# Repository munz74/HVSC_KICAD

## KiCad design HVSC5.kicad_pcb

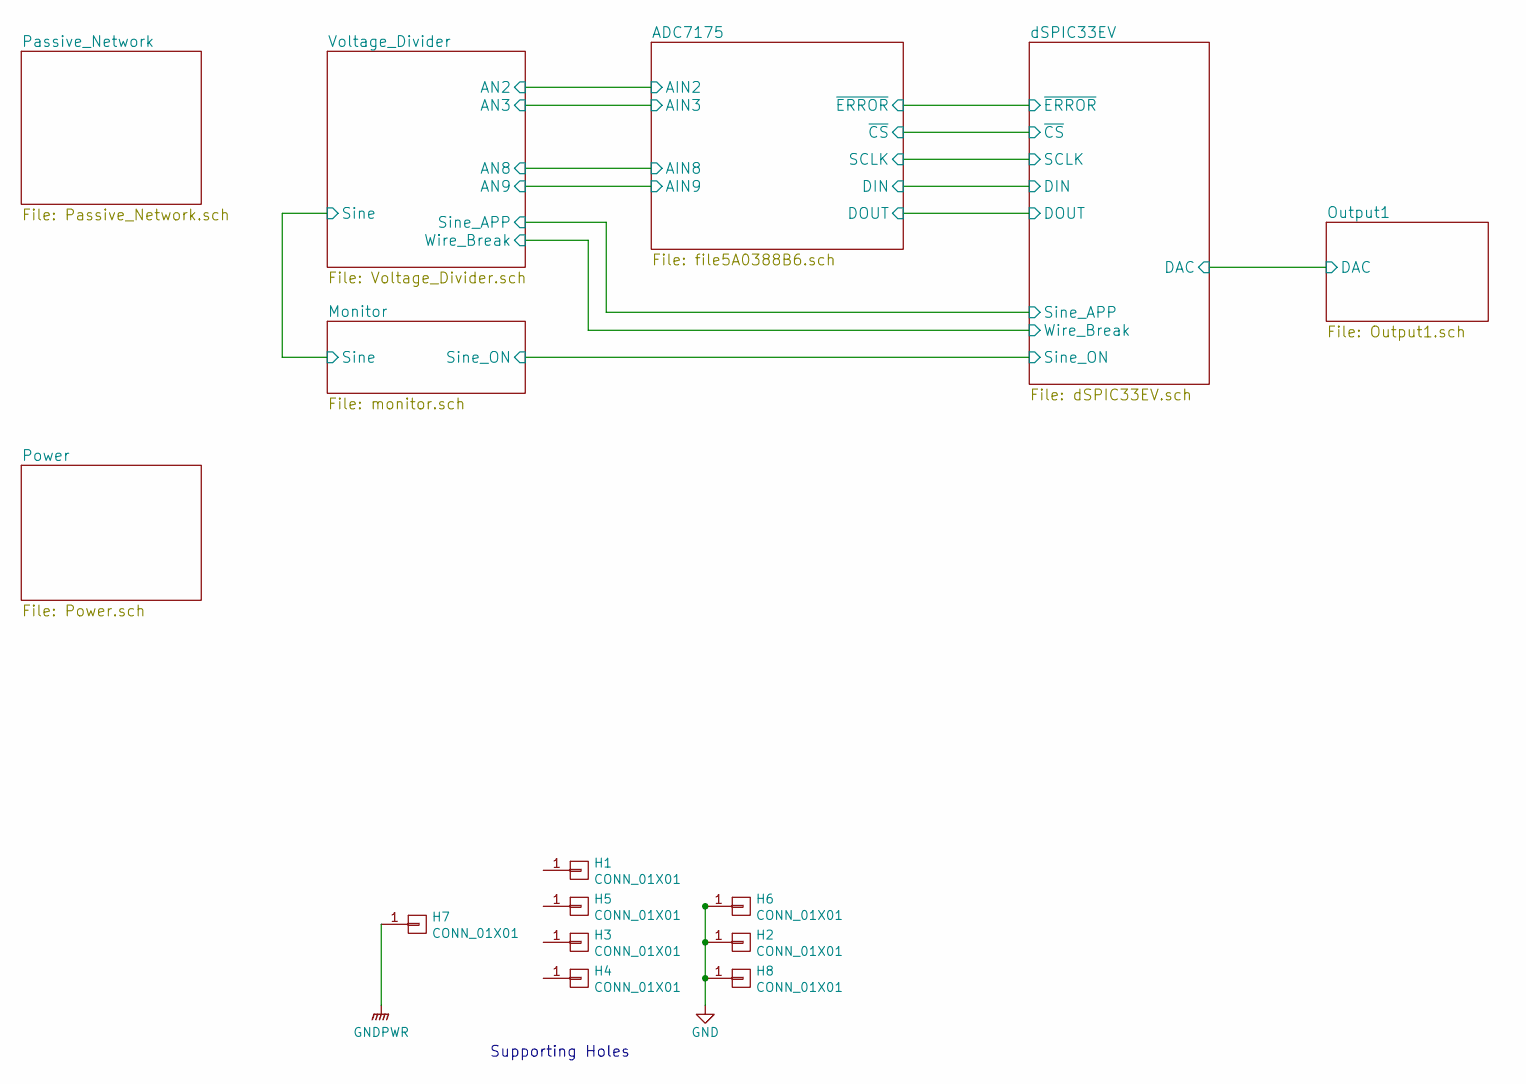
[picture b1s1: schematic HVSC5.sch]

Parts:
H1, H2, H3, H4, H5, H6, H7, H8: CONN_01X01; MountingHole_3.2mm_M3_Pad_Via

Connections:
GND: H2.1, H6.1, H8.1; also elsewhere on the board
GNDPWR: H7.1; also elsewhere on the board

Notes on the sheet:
Supporting Holes

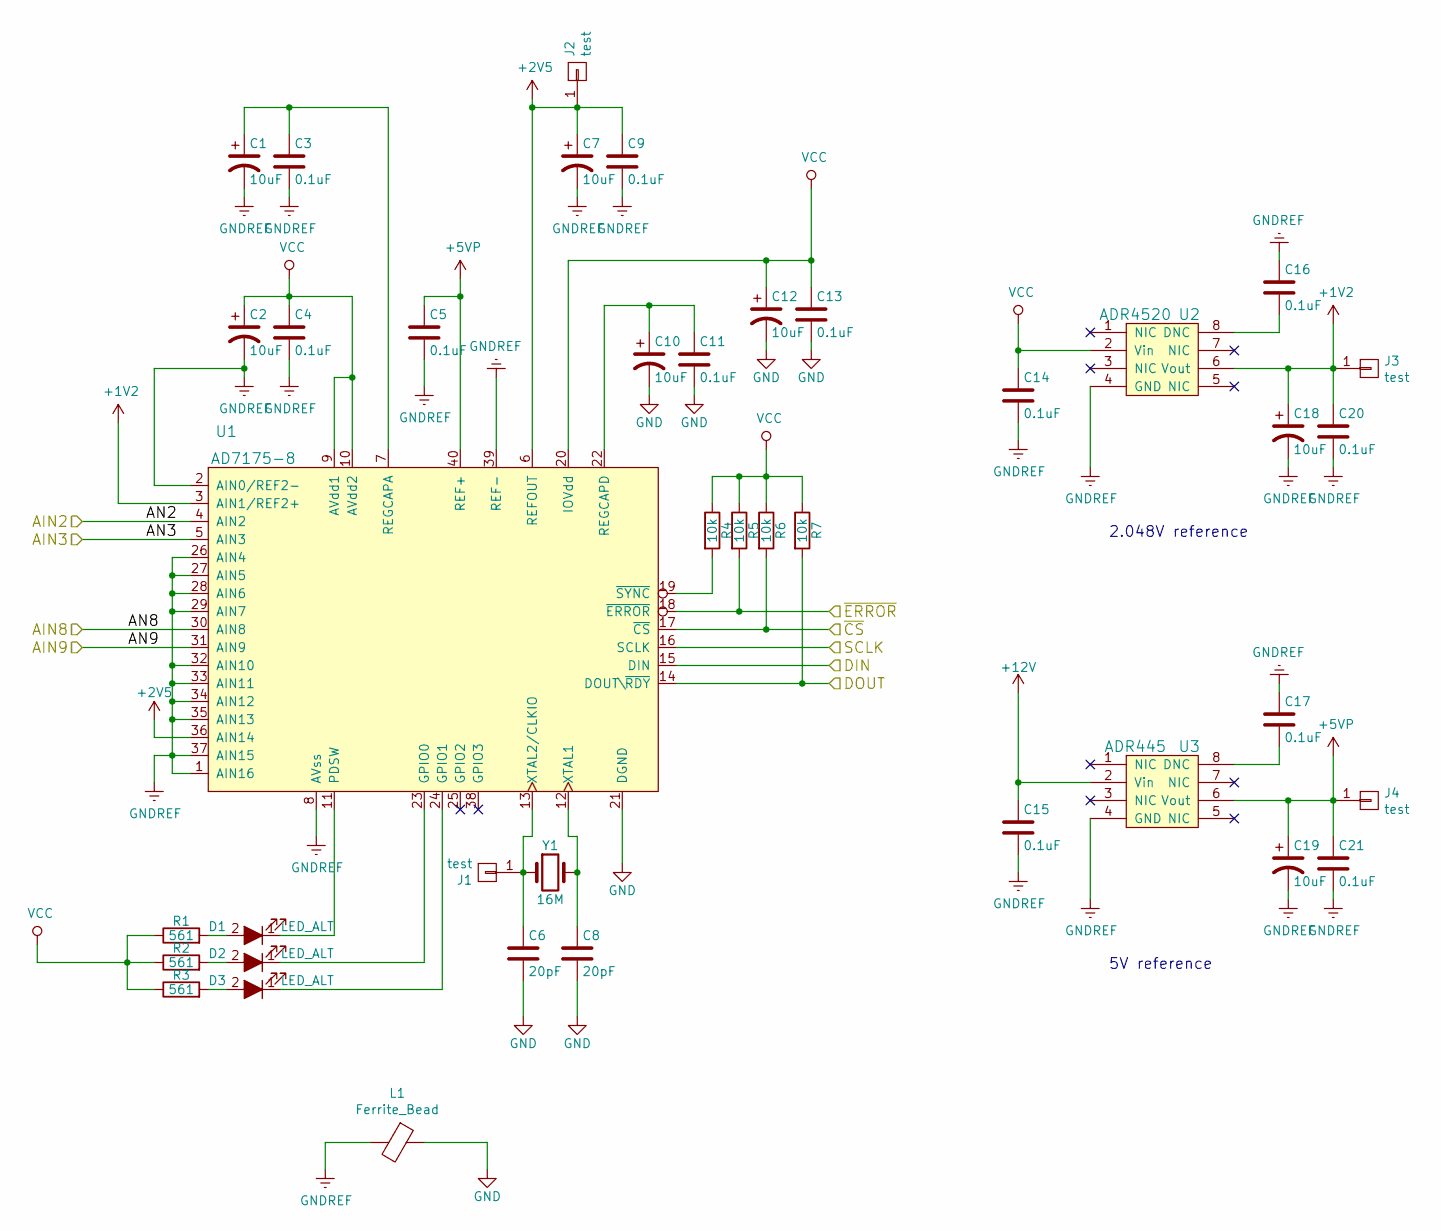
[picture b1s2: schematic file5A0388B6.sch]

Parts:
C1, C2, C7, C10, C12, C18, C19: 10uF; C_1812_HandSoldering_Polar
C3, C4, C5, C9, C11, C13, C14, C15, C16, C17, C20, C21: 0.1uF; C_0805_HandSoldering
C6, C8: 20pF; C_0805_HandSoldering
D1, D2, D3: LED_ALT; LED_0603_HandSoldering
J1, J2, J3, J4: test; Pin_Header_Straight_1x01_Pitch2.00mm
L1: Ferrite_Bead; L_1806_Handsoldering
R1, R2, R3: 561; R_0805_HandSoldering
R4, R5, R6, R7: 10k; R_0805_HandSoldering
U1: AD7175-8; LFCSP-40-1EP_long
U2: ADR4520; SOIC-8_3.9x4.9mm_Pitch1.27mm
U3: ADR445; SOIC-8_3.9x4.9mm_Pitch1.27mm
Y1: 16M; Crystal_HC49-4H_Vertical

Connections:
+1V2: C18.1, C20.1, J3.1, U1.3 (AIN1/REF2+), U2.6 (Vout)
+2V5: C7.1, C9.1, J2.1, U1.6 (REFOUT), U1.36 (AIN14); also elsewhere on the board
+5VP: C5.1, C19.1, C21.1, J4.1, U1.40 (REF+), U3.6 (Vout)
+12V: C15.1, U3.2 (Vin); also elsewhere on the board
/ADC7175/AIN2: U1.4 (AIN2); also elsewhere on the board
/ADC7175/AIN3: U1.5 (AIN3); also elsewhere on the board
/ADC7175/AIN8: U1.30 (AIN8); also elsewhere on the board
/ADC7175/AIN9: U1.31 (AIN9); also elsewhere on the board
/ADC7175/DIN: U1.15 (DIN); also elsewhere on the board
/ADC7175/DOUT: R7.2, U1.14 (DOUT\~RDY); also elsewhere on the board
/ADC7175/SCLK: U1.16 (SCLK); also elsewhere on the board
/ADC7175/~CS: R6.2, U1.17 (~CS); also elsewhere on the board
/ADC7175/~ERROR: R5.2, U1.18 (~ERROR); also elsewhere on the board
GND: C6.2, C8.2, C10.2, C11.2, C12.2, C13.2, L1.1, U1.21 (DGND); also elsewhere on the board
GNDREF: C1.2, C2.2, C3.2, C4.2, C5.2, C7.2, C9.2, C14.2, C15.2, C16.1, C17.1, C18.2, C19.2, C20.2, C21.2, L1.2, U1.1 (AIN16), U1.2 (AIN0/REF2-), U1.8 (AVss), U1.26 (AIN4), U1.27 (AIN5), U1.28 (AIN6), U1.29 (AIN7), U1.32 (AIN10), U1.33 (AIN11), U1.34 (AIN12), U1.35 (AIN13), U1.37 (AIN15), U1.39 (REF-), U2.4 (GND), U3.4 (GND); also elsewhere on the board
unnamed: C1.1, C3.1, U1.7 (REGCAPA)
unnamed: C6.1, J1.1, U1.13 (XTAL2/CLKIO), Y1.1
unnamed: C8.1, U1.12 (XTAL1), Y1.2
unnamed: C10.1, C11.1, U1.22 (REGCAPD)
unnamed: C16.2, U2.8 (DNC)
unnamed: C17.2, U3.8 (DNC)
unnamed: D1.1 (K), U1.11 (PDSW)
unnamed: D1.2 (A), R1.2
unnamed: D2.1 (K), U1.23 (GPIO0)
unnamed: D2.2 (A), R2.2
unnamed: D3.1 (K), U1.24 (GPIO1)
unnamed: D3.2 (A), R3.2
unnamed: R4.2, U1.19 (~SYNC)
VCC: C2.1, C4.1, C12.1, C13.1, C14.1, R1.1, R2.1, R3.1, R4.1, R5.1, R6.1, R7.1, U1.9 (AVdd1), U1.10 (AVdd2), U1.20 (IOVdd), U2.2 (Vin); also elsewhere on the board

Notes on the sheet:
5V reference
2.048V reference

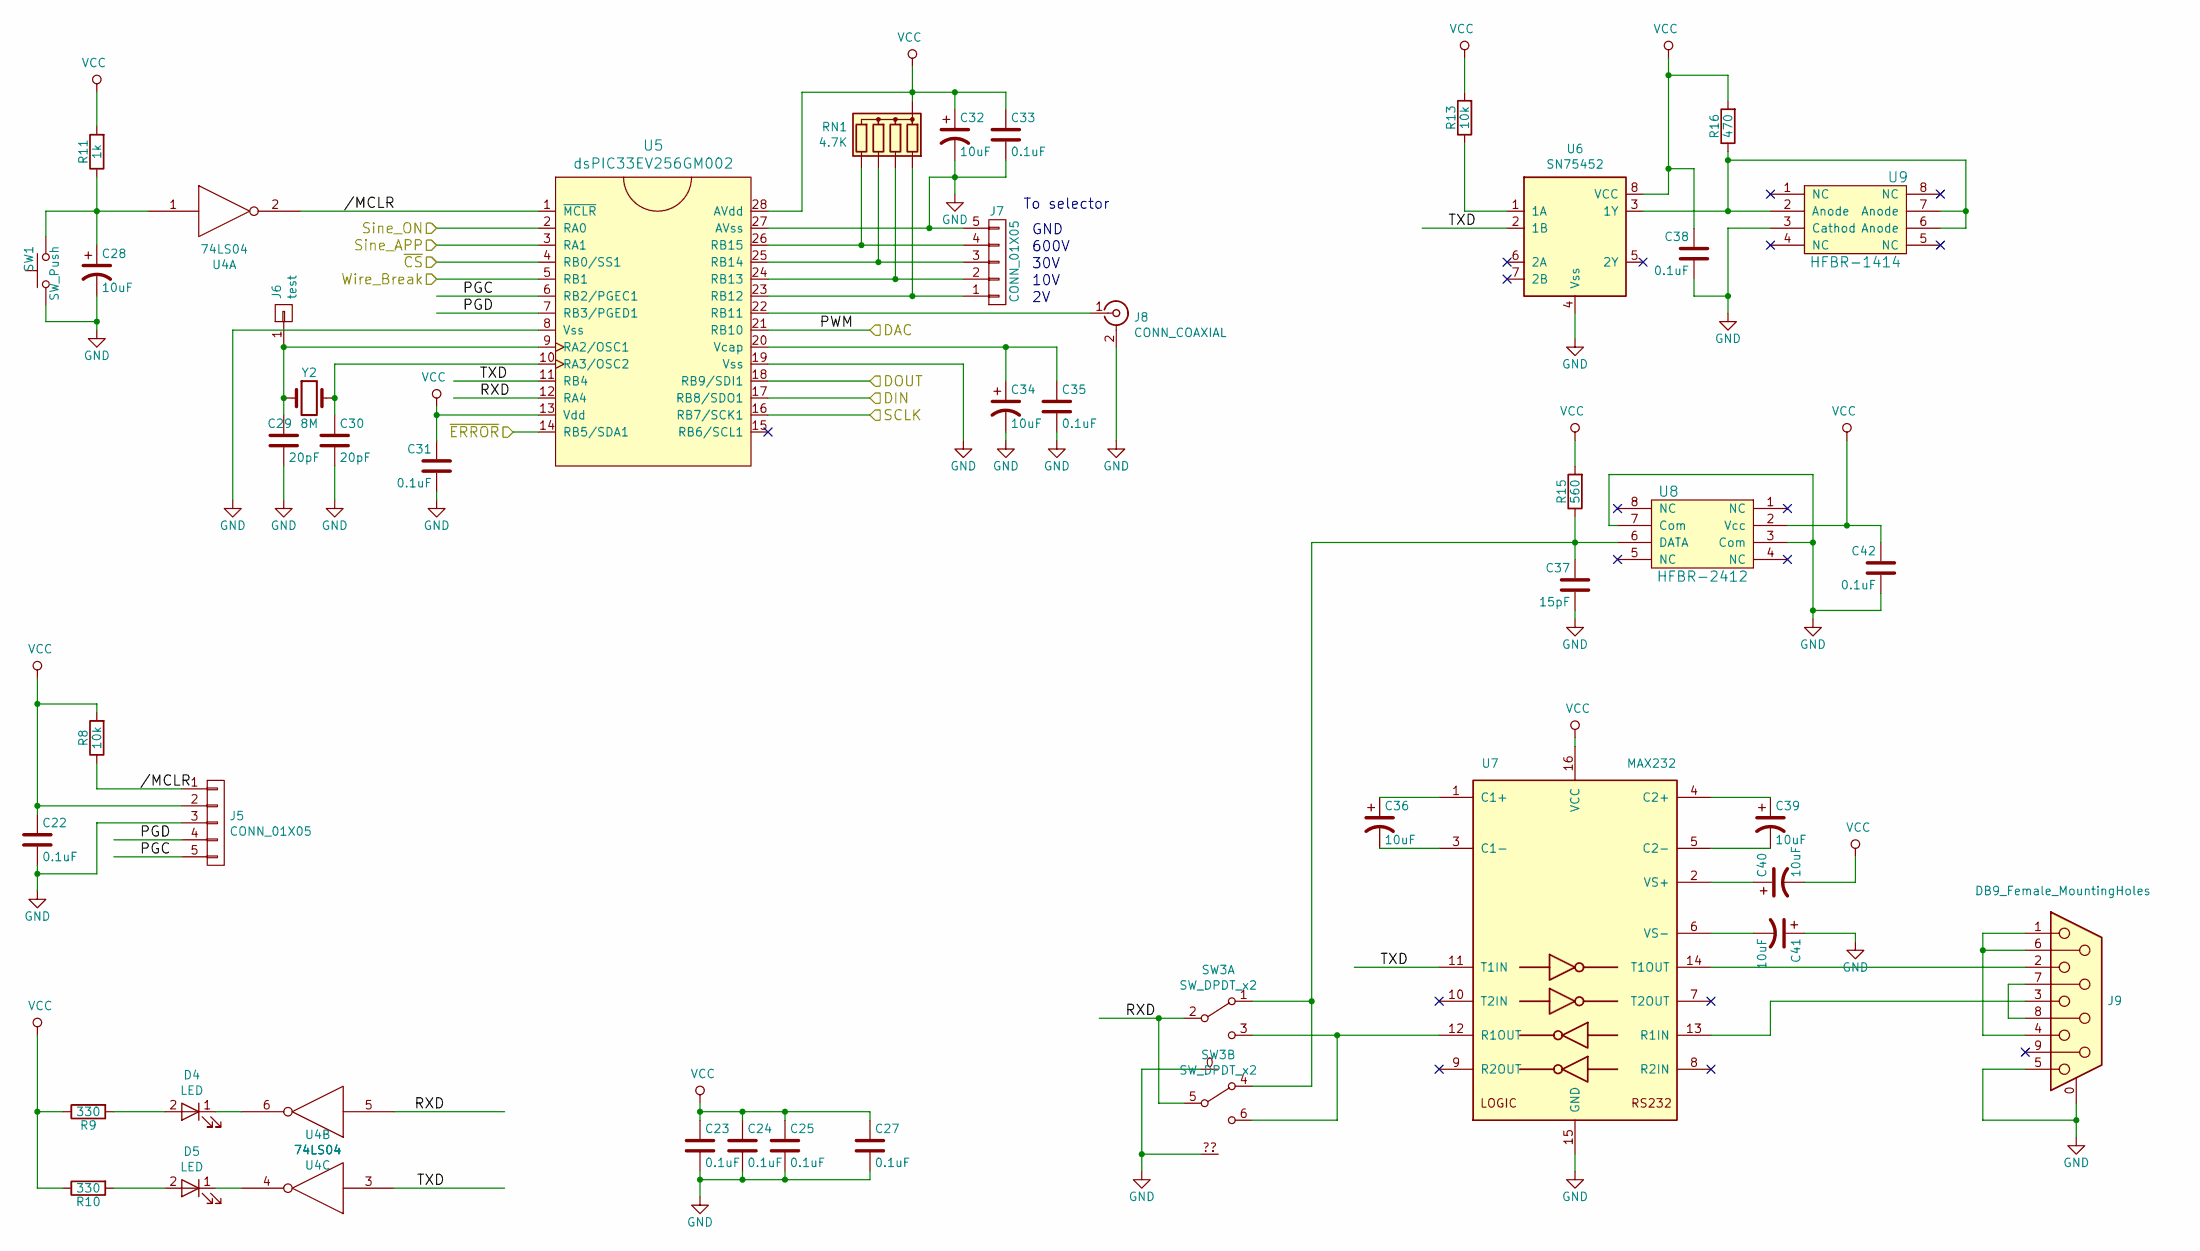
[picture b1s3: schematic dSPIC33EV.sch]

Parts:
C22, C23, C24, C25, C27, C31, C33, C35, C38, C42: 0.1uF; C_0805_HandSoldering
C28, C32, C34, C36, C39, C40, C41: 10uF; C_1812_HandSoldering_Polar
C29, C30: 20pF; C_0805_HandSoldering
C37: 15pF; C_0805_HandSoldering
D4, D5: LED; LED_D5.0mm
J5: CONN_01X05; Pin_Header_Straight_1x05_Pitch2.54mm
J6: test; Pin_Header_Straight_1x01_Pitch2.00mm
J7: CONN_01X05; M53259-5
J8: CONN_COAXIAL; bnc-ci
J9: DB9_Female_MountingHoles; DB_9F
R8, R13: 10k; R_0805_HandSoldering
R9, R10: 330; R_0805_HandSoldering
R11: 1k; R_0805_HandSoldering
R15: 560; R_0805_HandSoldering
R16: 470; R_Axial_DIN0207_L6.3mm_D2.5mm_P10.16mm_Horizontal
RN1: 4.7K; R_Array_SIP5
SW1: SW_Push; SW_Tactile_SPST_PTS645Vx58-2
SW3: SW_DPDT_x2; SW_E-Switch_EG2219_DPDT
U4: 74LS04; DIP-14_W7.62mm_Socket
U5: dsPIC33EV256GM002; SSOP-28_5.3x10.2mm_Pitch0.65mm
U6: SN75452; DIP-8_W7.62mm
U7: MAX232; DIP-16_W7.62mm
U8: HFBR-2412; HFBR-1414
U9: HFBR-1414
Y2: 8M; Crystal_HC49-4H_Vertical

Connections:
/ADC7175/DIN: U5.17 (RB8/SDO1); also elsewhere on the board
/ADC7175/DOUT: U5.18 (RB9/SDI1); also elsewhere on the board
/ADC7175/SCLK: U5.16 (RB7/SCK1); also elsewhere on the board
/ADC7175/~CS: U5.4 (RB0/SS1); also elsewhere on the board
/ADC7175/~ERROR: U5.14 (RB5/SDA1); also elsewhere on the board
/Monitor/Sine_ON: U5.2 (RA0); also elsewhere on the board
/Output1/DAC: U5.21 (RB10); also elsewhere on the board
/Voltage_Divider/Sine_APP: U5.3 (RA1); also elsewhere on the board
/Voltage_Divider/Wire_Break: U5.5 (RB1); also elsewhere on the board
/dSPIC33EV//MCLR: J5.1, R8.1, U4.2, U5.1 (~MCLR)
/dSPIC33EV/PGC: J5.5, U5.6 (RB2/PGEC1)
/dSPIC33EV/PGD: J5.4, U5.7 (RB3/PGED1)
/dSPIC33EV/RXD: SW3.2 (B), SW3.5 (B), U4.5, U5.12 (RA4)
/dSPIC33EV/TXD: U4.3, U5.11 (RB4), U6.2 (1B), U7.11 (T1IN)
GND: C22.2, C23.2, C24.2, C25.2, C27.2, C28.2, C29.2, C30.2, C31.2, C32.2, C33.2, C34.2, C35.2, C37.2, C38.2, C41.1, C42.2, J5.3, J7.5, J8.2 (Ext), J9.0 (PAD), J9.5, SW1.1, SW3.0 (GND), SW3.?? (GND), U4.7 (GND), U5.8 (Vss), U5.19 (Vss), U5.27 (AVss), U6.4 (Vss), U7.15 (GND), U8.3 (Com), U8.7 (Com), U9.3 (Cathod); also elsewhere on the board
unnamed: C28.1, R11.1, SW1.2, U4.1
unnamed: C29.1, J6.1, U5.9 (RA2/OSC1), Y2.1
unnamed: C30.1, U5.10 (RA3/OSC2), Y2.2
unnamed: C34.1, C35.1, U5.20 (Vcap)
unnamed: C36.1, U7.1 (C1+)
unnamed: C36.2, U7.3 (C1-)
unnamed: C37.1, R15.1, SW3.1 (A), SW3.4 (A), U8.6 (DATA)
unnamed: C39.1, U7.4 (C2+)
unnamed: C39.2, U7.5 (C2-)
unnamed: C40.1, U7.2 (VS+)
unnamed: C41.2, U7.6 (VS-)
unnamed: D4.1 (K), U4.6
unnamed: D4.2 (A), R9.2
unnamed: D5.1 (K), U4.4
unnamed: D5.2 (A), R10.2
unnamed: J7.1, RN1.2 (R1), U5.23 (RB12)
unnamed: J7.2, RN1.3 (R2), U5.24 (RB13)
unnamed: J7.3, RN1.4 (R3), U5.25 (RB14)
unnamed: J7.4, RN1.5 (R4), U5.26 (RB15)
unnamed: J8.1 (In), U5.22 (RB11)
unnamed: J9.1, J9.4, J9.6
unnamed: J9.2, U7.14 (T1OUT)
unnamed: J9.3, U7.13 (R1IN)
unnamed: J9.7, J9.8
unnamed: R13.1, U6.1 (1A)
unnamed: R16.1, U6.3 (1Y), U9.2 (Anode), U9.6 (Anode), U9.7 (Anode)
unnamed: SW3.3 (C), SW3.6 (C), U7.12 (R1OUT)
VCC: C22.1, C23.1, C24.1, C25.1, C27.1, C31.1, C32.1, C33.1, C38.1, C40.2, C42.1, J5.2, R8.2, R9.1, R10.1, R11.2, R13.2, R15.2, R16.2, RN1.1 (common), U4.14 (VCC), U5.13 (Vdd), U5.28 (AVdd), U6.8 (VCC), U7.16 (VCC), U8.2 (Vcc); also elsewhere on the board

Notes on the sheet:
To selector
600V
30V
10V
GND

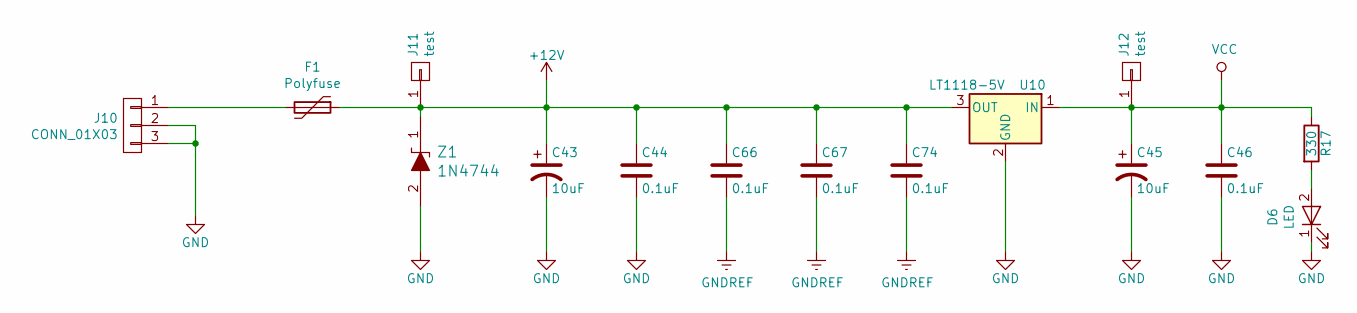
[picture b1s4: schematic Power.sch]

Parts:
C43, C45: 10uF; C_1812_HandSoldering_Polar
C44, C46, C66, C67, C74: 0.1uF; C_0805_HandSoldering
D6: LED; LED_D5.0mm
F1: Polyfuse; Fuse_CB61F
J10: CONN_01X03; M53259-3
J11, J12: test; Pin_Header_Straight_1x01_Pitch2.00mm
R17: 330; R_0805_HandSoldering
U10: LT1118-5V; SOT-223_LT1118
Z1: 1N4744; D_SMA-SMB_Universal_Handsoldering; MPN 1N5231BTR; Digi-Key_PN 1N5231BFSCT-ND

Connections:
+12V: C43.1, C44.1, C66.1, C67.1, C74.1, F1.1, J11.1, U10.3 (OUT), Z1.1; also elsewhere on the board
GND: C43.2, C44.2, C45.2, C46.2, D6.1 (K), J10.2, J10.3, U10.2 (GND), Z1.2; also elsewhere on the board
GNDREF: C66.2, C67.2, C74.2; also elsewhere on the board
unnamed: D6.2 (A), R17.2
unnamed: F1.2, J10.1
VCC: C45.1, C46.1, J12.1, R17.1, U10.1 (IN); also elsewhere on the board

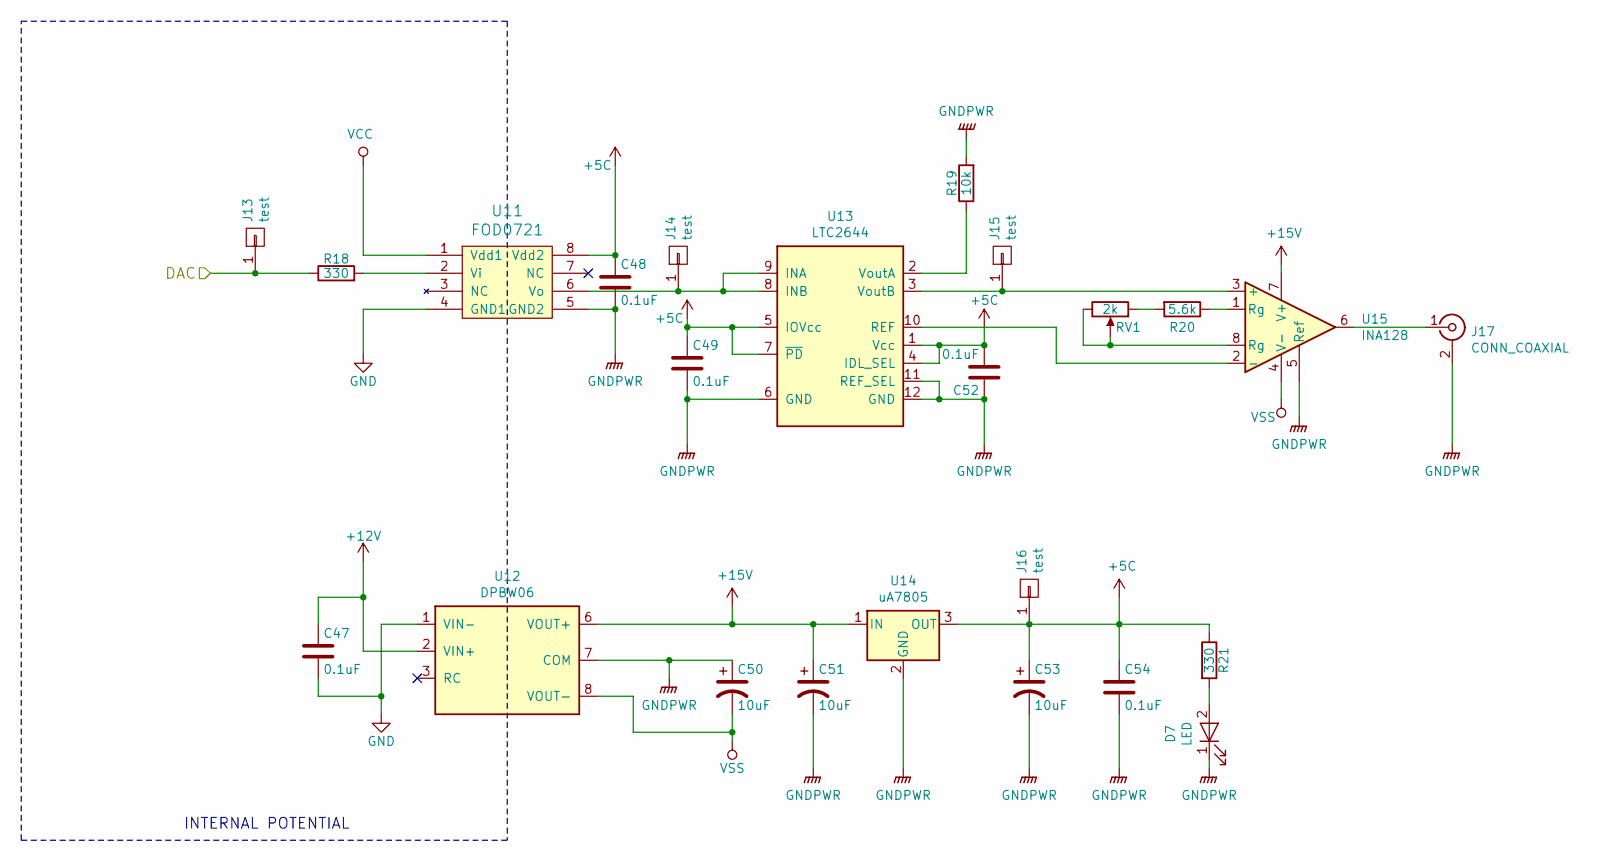
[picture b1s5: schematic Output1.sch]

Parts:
C47, C48, C49, C52, C54: 0.1uF; C_0805_HandSoldering
C50, C51, C53: 10uF; C_1812_HandSoldering_Polar
D7: LED; LED_D5.0mm
J13, J14, J15, J16: test; Pin_Header_Straight_1x01_Pitch2.00mm
J17: CONN_COAXIAL; Molex_KK-6410-02_02x2.54mm_Straight
R18, R21: 330; R_0805_HandSoldering
R19: 10k; R_0805_HandSoldering
R20: 5.6k; R_0805_HandSoldering
RV1: 2k; Potentiometer_Trimmer_Bourns_3296W
U11: FOD0721; SOIC-8_3.9x4.9mm_Pitch1.27mm
U12: DPBW06; DCDC-Conv_SPBW06
U13: LTC2644; MSOP-12-1EP_3x4mm_Pitch0.65mm
U14: uA7805; TO-263-2
U15: INA128; DIP-8_W7.62mm_Socket

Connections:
+12V: C47.1, U12.2 (VIN+); also elsewhere on the board
+15V: C51.1, U12.6 (VOUT+), U14.1 (IN), U15.7 (V+)
/Output1/DAC: J13.1, R18.1; also elsewhere on the board
GND: C47.2, U11.4 (GND1), U12.1 (VIN-); also elsewhere on the board
GNDPWR: C48.2, C49.2, C50.1, C51.2, C52.1, C53.2, C54.2, D7.1 (K), J17.2 (Ext), R19.2, U11.5 (GND2), U12.7 (COM), U13.6 (GND), U13.11 (REF_SEL), U13.12 (GND), U14.2 (GND), U15.5 (Ref); also elsewhere on the board
unnamed: D7.2 (A), R21.2
unnamed: J14.1, U11.6 (Vo), U13.8 (INB), U13.9 (INA)
unnamed: J15.1, U13.3 (VoutB), U15.3 (+)
unnamed: J17.1 (In), U15.6
unnamed: R18.2, U11.2 (Vi)
unnamed: R19.1, U13.2 (VoutA)
unnamed: R20.1, U15.1 (Rg)
unnamed: R20.2, RV1.1
unnamed: RV1.2, RV1.3, U15.8 (Rg)
VCC: U11.1 (Vdd1); also elsewhere on the board
VSS: C50.2, U12.8 (VOUT-), U15.4 (V-)

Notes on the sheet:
INTERNAL POTENTIAL

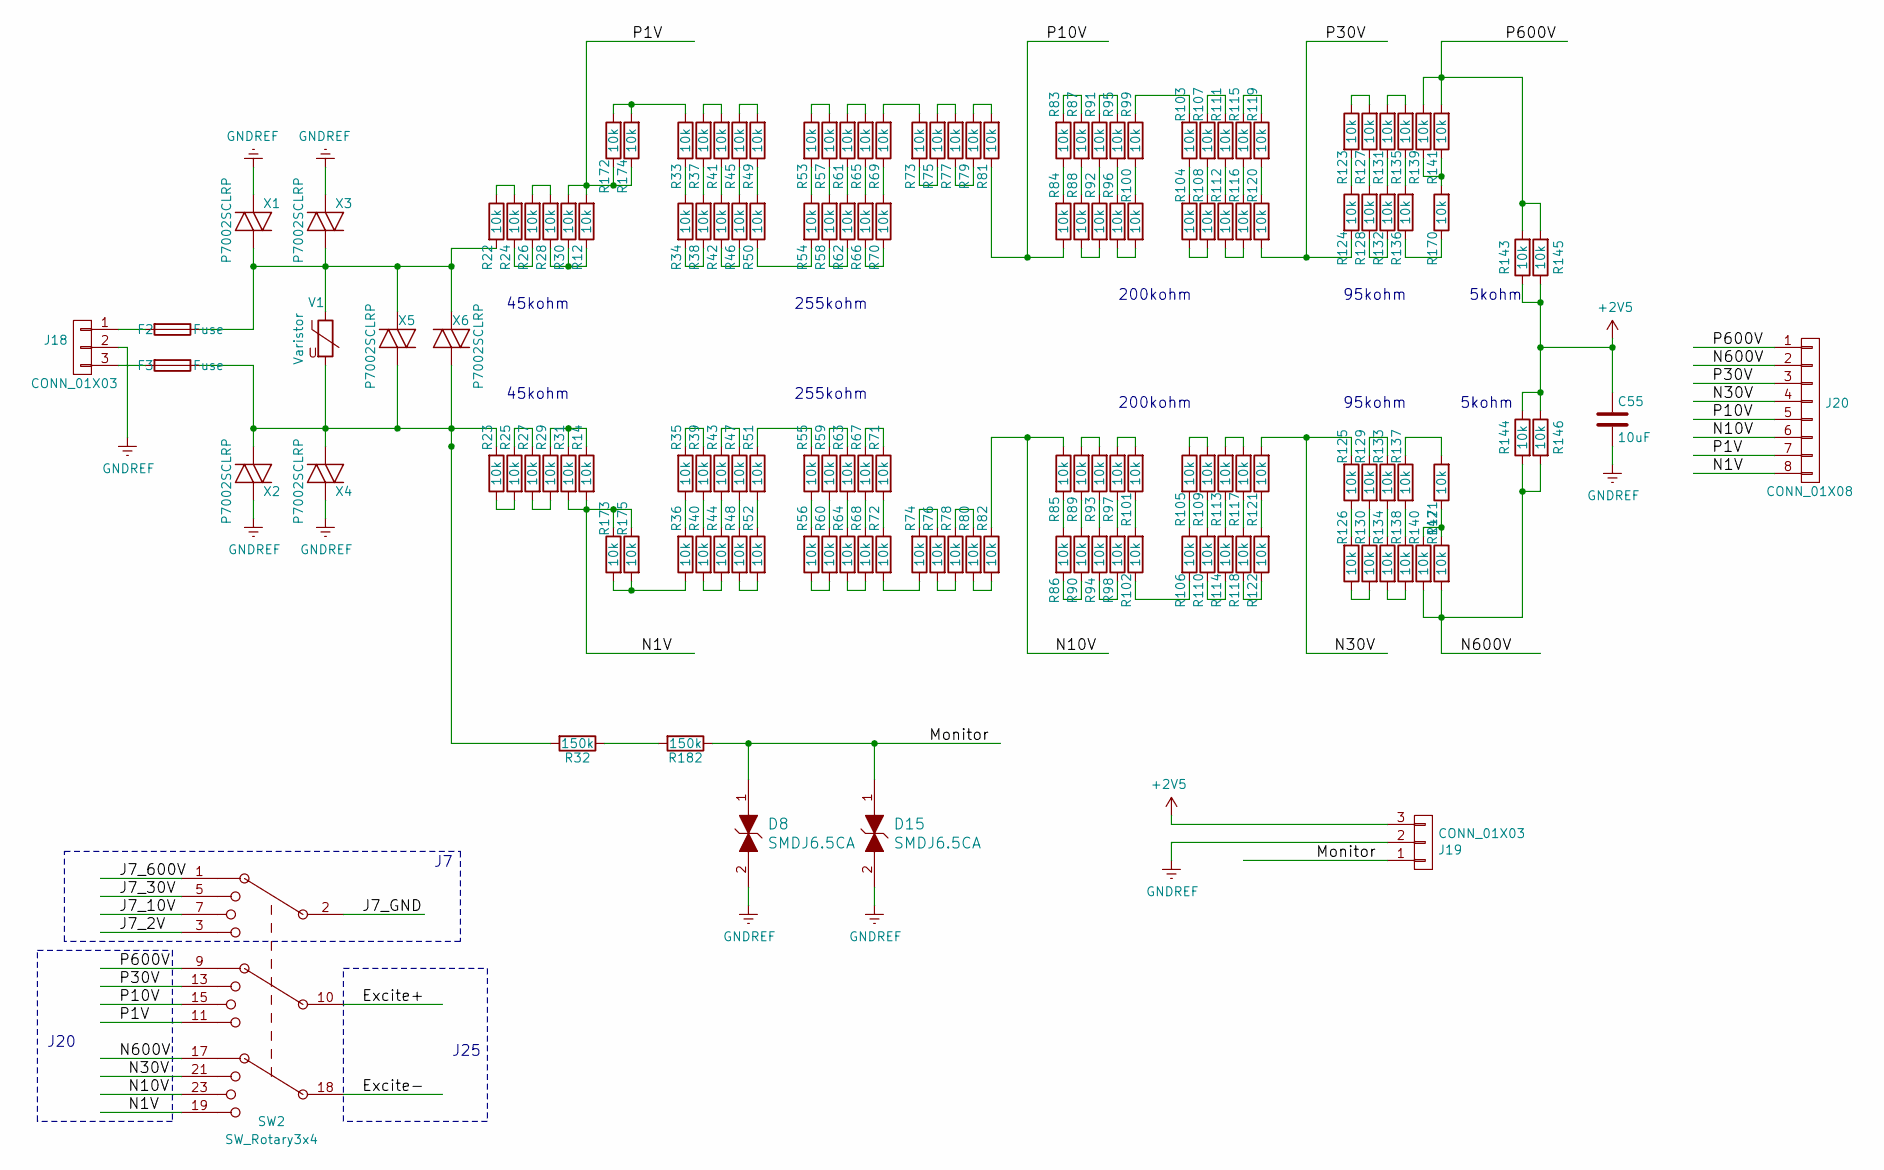
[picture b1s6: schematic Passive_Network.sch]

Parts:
C55: 10uF; C_1210_HandSoldering
D8, D15: SMDJ6.5CA; D_SMC_Handsoldering; MPN PGB1010603MR; Digi-Key_PN F2594CT-ND
F2, F3: Fuse; Fuseholder6x32_Horiz_Open_Schurter0031-8002
J18: CONN_01X03; BR762-3
J19: CONN_01X03; M53259-3
J20: CONN_01X08; BR762-8
R12, R14, R22, R23, R24, R25, R26, R27, R28, R29, R30, R31, R33, R34, R35, R36, R37, R38, R39, R40, R41, R42, R43, R44, R45, R46, R47, R48, R49, R50, R51, R52, R53, R54, R55, R56, R57, R58, R59, R60, R61, R62, R63, R64, R65, R66, R67, R68, R69, R70, R71, R72, R73, R74, R75, R76, R77, R78, R79, R80, R81, R82, R83, R84, R85, R86, R87, R88, R89, R90, R91, R92, R93, R94, R95, R96, R97, R98, R99, R100, R101, R102, R103, R104, R105, R106, R107, R108, R109, R110, R111, R112, R113, R114, R115, R116, R117, R118, R119, R120, R121, R122, R123, R124, R125, R126, R127, R128, R129, R130, R131, R132, R133, R134, R135, R136, R137, R138, R139, R140, R141, R142, R143, R144, R145, R146, R170, R171, R172, R173, R174, R175: 10k; R_1206_HandSoldering
R32, R182: 150k; R_Axial_Power_L20.0mm_W6.4mm_P22.40mm
SW2: SW_Rotary3x4
V1: Varistor; RV_Disc_D12_W4_P7.5
X1, X2, X3, X4, X5, X6: P7002SCLRP; D_SMA-SMB_Universal_Handsoldering

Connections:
+2V5: C55.1, J19.3, R143.1, R144.1, R145.1, R146.1; also elsewhere on the board
/Passive_Network/Monitor: D8.1, D15.1, J19.1, R182.1
/Passive_Network/N1V: J20.8, R14.2, R31.2, R173.1, R175.1, SW2.19
/Passive_Network/N10V: J20.6, R82.1, R85.1, SW2.23
/Passive_Network/N30V: J20.4, R121.2, R125.2, SW2.21
/Passive_Network/N600V: J20.2, R140.2, R142.2, R144.2, R146.2, SW2.17
/Passive_Network/P1V: J20.7, R12.2, R30.2, R172.1, R174.1, SW2.11
/Passive_Network/P10V: J20.5, R81.1, R84.1, SW2.15
/Passive_Network/P30V: J20.3, R120.2, R124.2, SW2.13
/Passive_Network/P600V: J20.1, R139.2, R141.2, R143.2, R145.2, SW2.9
GNDREF: C55.2, D8.2, D15.2, J18.2, J19.2, X1.1 (K), X2.2 (A), X3.1 (K), X4.2 (A); also elsewhere on the board
unnamed 94: F2.1, R22.2, V1.1, X1.2 (A), X3.2 (A), X5.1 (K), X6.1 (K); also elsewhere on the board
unnamed: F2.2, J18.1
unnamed: F3.1, R23.2, R32.2, V1.2, X2.1 (K), X4.1 (K), X5.2 (A), X6.2 (A)
unnamed: F3.2, J18.3
unnamed: R12.1, R28.1, R30.1
unnamed: R14.1, R29.1, R31.1
unnamed: R22.1, R24.2
unnamed: R23.1, R25.2
unnamed: R24.1, R26.1
unnamed: R25.1, R27.1
unnamed: R26.2, R28.2
unnamed: R27.2, R29.2
unnamed: R33.2, R34.1
unnamed: R34.2, R38.1
unnamed: R35.1, R36.2
unnamed: R35.2, R39.1
unnamed: R37.1, R38.2
unnamed: R37.2, R41.2
unnamed: R39.2, R40.1
unnamed: R40.2, R44.2
unnamed: R41.1, R42.2
unnamed: R42.1, R46.1
unnamed: R43.1, R47.1
unnamed: R43.2, R44.1
unnamed: R45.1, R46.2
unnamed: R45.2, R49.2
unnamed: R47.2, R48.1
unnamed: R48.2, R52.2
unnamed: R49.1, R50.2
unnamed: R50.1, R54.2
unnamed: R51.1, R55.2
unnamed: R51.2, R52.1
unnamed: R53.1, R57.2
unnamed: R53.2, R54.1
unnamed: R55.1, R56.2
unnamed: R56.1, R60.2
unnamed: R57.1, R58.2
unnamed: R58.1, R62.1
unnamed: R59.1, R63.1
unnamed: R59.2, R60.1
unnamed: R61.1, R62.2
unnamed: R61.2, R65.2
unnamed: R63.2, R64.1
unnamed: R64.2, R68.2
unnamed: R65.1, R66.2
unnamed: R66.1, R70.1
unnamed: R67.1, R71.1
unnamed: R67.2, R68.1
unnamed: R69.1, R70.2
unnamed: R69.2, R73.1
unnamed: R71.2, R72.1
unnamed: R72.2, R74.1
unnamed: R73.2, R75.1
unnamed: R74.2, R76.1
unnamed: R75.2, R77.2
unnamed: R76.2, R78.2
unnamed: R77.1, R79.1
unnamed: R78.1, R80.1
unnamed: R79.2, R81.2
unnamed: R80.2, R82.2
unnamed: R83.1, R84.2
unnamed: R83.2, R87.1
unnamed: R85.2, R86.1
unnamed: R86.2, R90.1
unnamed: R87.2, R88.1
unnamed: R88.2, R92.2
unnamed: R89.1, R90.2
unnamed: R89.2, R93.2
unnamed: R91.1, R95.1
unnamed: R91.2, R92.1
unnamed: R93.1, R94.2
unnamed: R94.1, R98.1
unnamed: R95.2, R96.1
unnamed: R97.1, R98.2
unnamed: R99.2, R100.1
unnamed: R96.2, R100.2
unnamed: R101.1, R102.2
unnamed: R97.2, R101.2
unnamed: R102.1, R106.2
unnamed: R103.1, R104.2
unnamed: R99.1, R103.2
unnamed: R104.1, R108.2
unnamed: R105.1, R109.2
unnamed: R105.2, R106.1
unnamed: R107.1, R111.1
unnamed: R107.2, R108.1
unnamed: R109.1, R110.2
unnamed: R110.1, R114.1
unnamed: R111.2, R112.1
unnamed: R112.2, R116.2
unnamed: R113.1, R114.2
unnamed: R113.2, R117.2
unnamed: R115.1, R119.1
unnamed: R115.2, R116.1
unnamed: R117.1, R118.2
unnamed: R118.1, R122.1
unnamed: R119.2, R120.1
unnamed: R121.1, R122.2
unnamed: R123.1, R127.2
unnamed: R123.2, R124.1
unnamed: R125.1, R126.2
unnamed: R126.1, R130.2
unnamed: R127.1, R128.2
unnamed: R128.1, R132.1
unnamed: R129.1, R133.1
unnamed: R129.2, R130.1
unnamed: R131.1, R132.2
unnamed: R131.2, R135.2
unnamed: R133.2, R134.1
unnamed: R134.2, R138.2
unnamed: R135.1, R136.2
unnamed: R136.1, R170.1
unnamed: R137.1, R171.2
unnamed: R137.2, R138.1
unnamed: R139.1, R141.1, R170.2
unnamed: R140.1, R142.1, R171.1
unnamed: R33.1, R172.2, R174.2
unnamed: R36.1, R173.2, R175.2
unnamed: R32.1, R182.2

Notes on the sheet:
45kohm
255kohm
200kohm
95kohm
5kohm
J20
J25

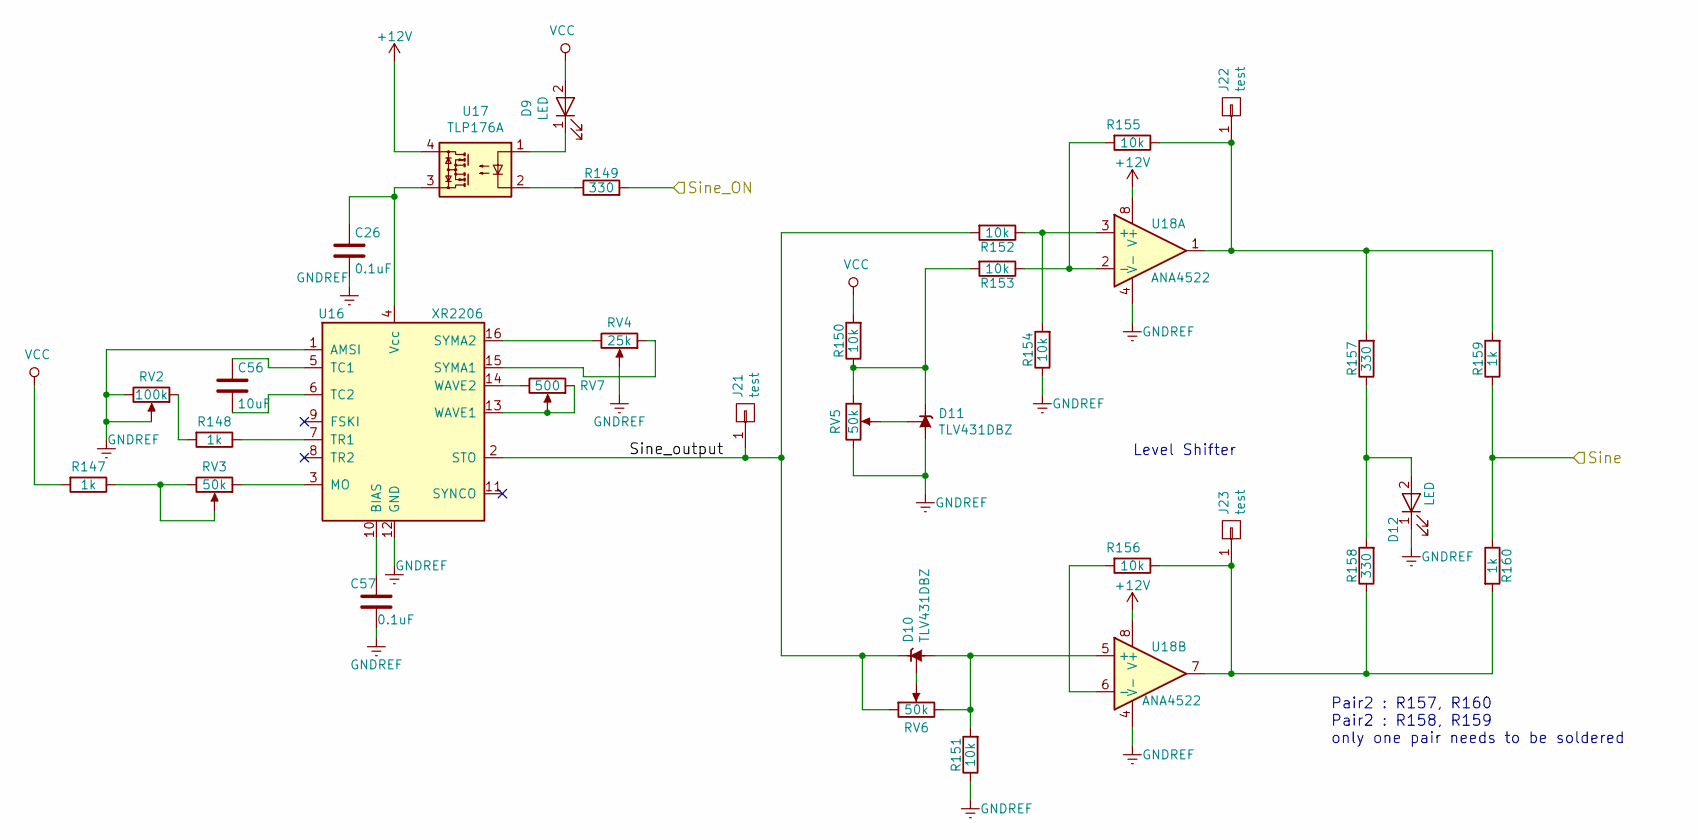
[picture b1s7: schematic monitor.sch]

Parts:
C26, C57: 0.1uF; C_0805_HandSoldering
C56: 10uF; C_1210_HandSoldering
D9, D12: LED; LED_D5.0mm
D10, D11: TLV431DBZ; SOT-23W_Handsoldering(LM431)
J21, J22, J23: test; Pin_Header_Straight_1x01_Pitch2.00mm
R147, R148, R159, R160: 1k; R_0805_HandSoldering
R149, R157, R158: 330; R_0805_HandSoldering
R150, R151, R152, R153, R154, R155, R156: 10k; R_0805_HandSoldering
RV2: 100k; Potentiometer_Trimmer_Bourns_3296W
RV3, RV5, RV6: 50k; Potentiometer_Trimmer_Bourns_3296W
RV4: 25k; Potentiometer_Trimmer_Bourns_3296W
RV7: 500; Potentiometer_Trimmer_Bourns_3296W
U16: XR2206; DIP-16_W7.62mm_Socket
U17: TLP176A; SO-4_4.4x4.3mm_Pitch2.54mm_Hand_Soldering
U18: ANA4522; SOIC-8_3.9x4.9mm_Pitch1.27mm

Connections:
+12V: U17.4, U18.8 (V+); also elsewhere on the board
/Monitor/Sine: R159.1, R160.1; also elsewhere on the board
/Monitor/Sine_ON: R149.2; also elsewhere on the board
/Monitor/Sine_output: D10.1 (K), J21.1, R152.2, RV6.1, U16.2 (STO)
GNDREF: C26.2, C57.2, D11.3 (A), D12.1 (K), R151.1, R154.1, RV2.2, RV2.3, RV4.2, RV5.3, U16.1 (AMSI), U16.12 (GND), U18.4 (V-); also elsewhere on the board
unnamed: C26.1, U16.4 (Vcc), U17.3
unnamed: C56.1, U16.5 (TC1)
unnamed: C56.2, U16.6 (TC2)
unnamed: C57.1, U16.10 (BIAS)
unnamed: D9.1 (K), U17.1
unnamed: D10.2 (REF), RV6.2
unnamed: D10.3 (A), R151.2, RV6.3, U18.5 (+)
unnamed: D11.1 (K), R150.1, R153.2, RV5.1
unnamed: D11.2 (REF), RV5.2
unnamed: D12.2 (A), R157.1, R158.2
unnamed: J22.1, R155.1, R157.2, R159.2, U18.1
unnamed: J23.1, R156.1, R158.1, R160.2, U18.7
unnamed: R147.1, RV3.2, RV3.3
unnamed: R148.1, U16.7 (TR1)
unnamed: R148.2, RV2.1
unnamed: R149.1, U17.2
unnamed: R152.1, R154.2, U18.3 (+)
unnamed: R153.1, R155.2, U18.2 (-)
unnamed: R156.2, U18.6 (-)
unnamed: RV3.1, U16.3 (MO)
unnamed: RV4.1, U16.15 (SYMA1)
unnamed: RV4.3, U16.16 (SYMA2)
unnamed: RV7.1, RV7.2, U16.13 (WAVE1)
unnamed: RV7.3, U16.14 (WAVE2)
VCC: D9.2 (A), R147.2, R150.2; also elsewhere on the board

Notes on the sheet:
Level Shifter
Pair2 : R157, R160 Pair2 : R158, R159 only one pair needs to be soldered
